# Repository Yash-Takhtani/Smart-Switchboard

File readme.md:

# Smart Switchboard
### Smart switchboard solves a unique problem. Usually smart devices require you to keep the switch on, making the switchboard useless. This smart switchboard solves that problem by making the switches smart directly.

# Features
 - This uses an ESP32 to control relays connected with my lights and a socket. I have a smart fan and the ESP32 will use its API to control the smart fan. 
 - It has 4 push buttons and a rotary encoder switch with RGB LEDs to control the devices.

# Quick Start
To replicate this project, you would want to follow these steps - 
 - Clone the repo and get the production files & firmware files
 - Get the model 3d printed from the .stl files
 - Take a look at the BOM and arrange the parts
 - Refer to the schematic folder and wire up the parts. (You have to have some soldering knowledge) **Be careful when handling wires from mains!**
 - Assemble all the components with non-conductive glue for electronics in the 3D printed model.
 - Enter your wifi credentials in the firmware.
 - Flash the firmware via micropico in the ESP32. 
 - Finally visit your ESP's local IP to access the control panel!

# Schematic
Here is the schematic. 

All the parts should be soldered directly since the microcontroller is to be kept a bit far away from the live AC current wires so that it works the best. Since the circuit is very simple and all the parts are supposed to be spaced out, a PCB is not required and the parts will be soldered directly.

# CAD model
 - This is the model to be 3D printed. It has holes to place the push buttons, LEDs and the rotary encoder switch

 - It also has space to stick a socket in the back. 

 - I measured everything like the screw holes, socket size and the borders with my existing switchboard to ensure everything fits in place

# Firmware
 - The firmware launches a webserver to control all the devices including 3 lights, a socket and a fan. 

 - I have a smart fan with a remote. I also have a IR blaster which I will use to control the fan. The code to control the fan via the IR blaster's API will not be pushed to github for obvious reasons. I dont want people around the world to control my fan. 

 - The firmware is made such that you could seamlessly switch the control between controlling from webserver or with physical buttons. The lights will also update in the switchboard as you change status of any device

# Build
**Check out the [demo video](https://www.youtube.com/shorts/NMJ9t9IXdI0)**

I completed the build and it works! 

I tested it out with a bulb only instead of installing it completely since there's not much I can do (I live in a rented place I am not supposed to mess with their switchboards)

# BOM
 - 1x  3D printed base
 - 1x  ESP32
 - 1x  Rotary Encoder Switch
 - 1x  5V 2A Power Supply
 - 4x  Push buttons
 - 4x  5V 30A Relays
 - 15x WS2812B RGB LEDs
 
For testing out stuff - 
 - 1x  Breadboard
 - 40x jumper wires

# Credits 
## Knob Model - [Jack](https://www.printables.com/model/243409-crown-knob/files)

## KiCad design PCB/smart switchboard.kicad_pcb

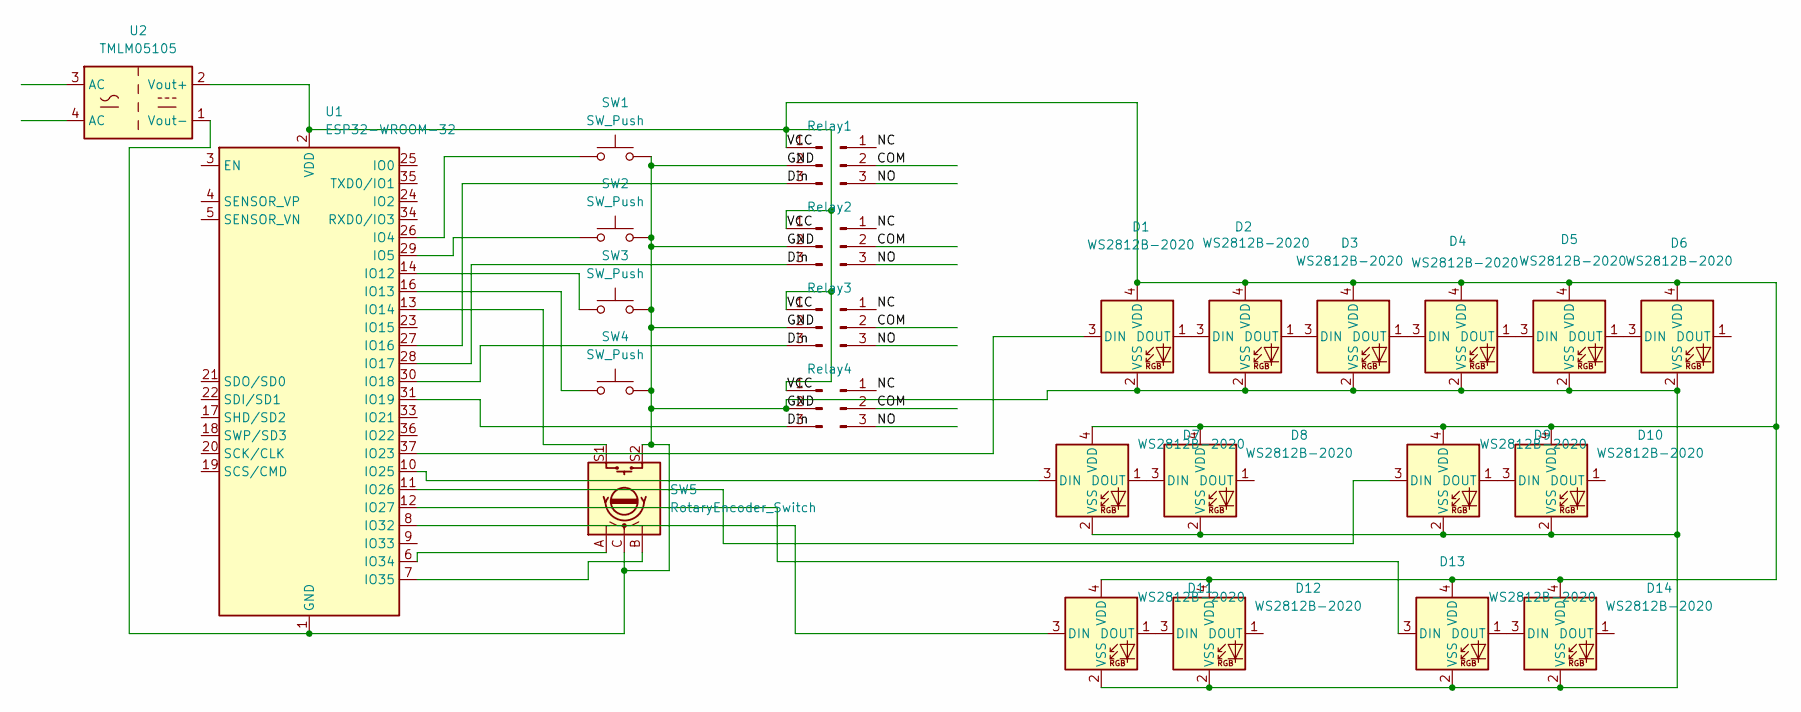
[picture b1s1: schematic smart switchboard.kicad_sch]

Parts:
D1, D2, D3, D4, D5, D6, D7, D8, D9, D10, D11, D12, D13, D14: WS2812B-2020; LED_WS2812B-2020_PLCC4_2.0x2.0mm
J3, J4, J5, J6: Conn_01x03_Pin; PinHeader_1x03_P2.00mm_Vertical
Relay1, Relay2, Relay3, Relay4: Conn_01x03_Pin; PinHeader_1x03_P2.00mm_Vertical
SW1, SW2, SW3, SW4: SW_Push; SW_PUSH_1P1T_6x3.5mm_H4.3_APEM_MJTP1243
SW5: RotaryEncoder_Switch; RotaryEncoder_Alps_EC11E-Switch_Vertical_H20mm
U1: ESP32-WROOM-32
U2: TMLM05105; Converter_ACDC_TRACO_TMLM-05_THT

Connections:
/COM: Relay1.2, Relay2.2, Relay3.2, Relay4.2
/Din: J3.3, J4.3, J5.3, J6.3, U1.27 (IO16), U1.28 (IO17), U1.30 (IO18), U1.31 (IO19)
/GND: D1.2 (VSS), D2.2 (VSS), D3.2 (VSS), D4.2 (VSS), D5.2 (VSS), D6.2 (VSS), D7.2 (VSS), D8.2 (VSS), D9.2 (VSS), D10.2 (VSS), D11.2 (VSS), D12.2 (VSS), D13.2 (VSS), D14.2 (VSS), J3.2, J4.2, J5.2, J6.2, SW1.2, SW2.2, SW3.2, SW4.2, SW5.C, SW5.S2, U1.1 (GND), U1.15 (GND), U1.38 (GND), U1.39 (GND), U2.1 (Vout-)
/NC: Relay1.1, Relay2.1, Relay3.1, Relay4.1
/NO: Relay1.3, Relay2.3, Relay3.3, Relay4.3
/VCC: D1.4 (VDD), D2.4 (VDD), D3.4 (VDD), D4.4 (VDD), D5.4 (VDD), D6.4 (VDD), D7.4 (VDD), D8.4 (VDD), D9.4 (VDD), D10.4 (VDD), D11.4 (VDD), D12.4 (VDD), D13.4 (VDD), D14.4 (VDD), J3.1, J4.1, J5.1, J6.1, U1.2 (VDD), U2.2 (Vout+)
unnamed: D1.3 (DIN), U1.37 (IO23)
unnamed: D1.1 (DOUT), D2.3 (DIN)
unnamed: D2.1 (DOUT), D3.3 (DIN)
unnamed: D3.1 (DOUT), D4.3 (DIN)
unnamed: D4.1 (DOUT), D5.3 (DIN)
unnamed: D5.1 (DOUT), D6.3 (DIN)
unnamed: D7.3 (DIN), U1.10 (IO25)
unnamed: D7.1 (DOUT), D8.3 (DIN)
unnamed: D9.3 (DIN), U1.11 (IO26)
unnamed: D9.1 (DOUT), D10.3 (DIN)
unnamed: D11.3 (DIN), U1.8 (IO32)
unnamed: D11.1 (DOUT), D12.3 (DIN)
unnamed: D13.3 (DIN), U1.12 (IO27)
unnamed: D13.1 (DOUT), D14.3 (DIN)
unnamed: SW1.1, U1.26 (IO4)
unnamed: SW2.1, U1.29 (IO5)
unnamed: SW3.1, U1.14 (IO12)
unnamed: SW4.1, U1.16 (IO13)
unnamed: SW5.S1, U1.13 (IO14)
unnamed: SW5.A, U1.6 (IO34)
unnamed: SW5.B, U1.7 (IO35)

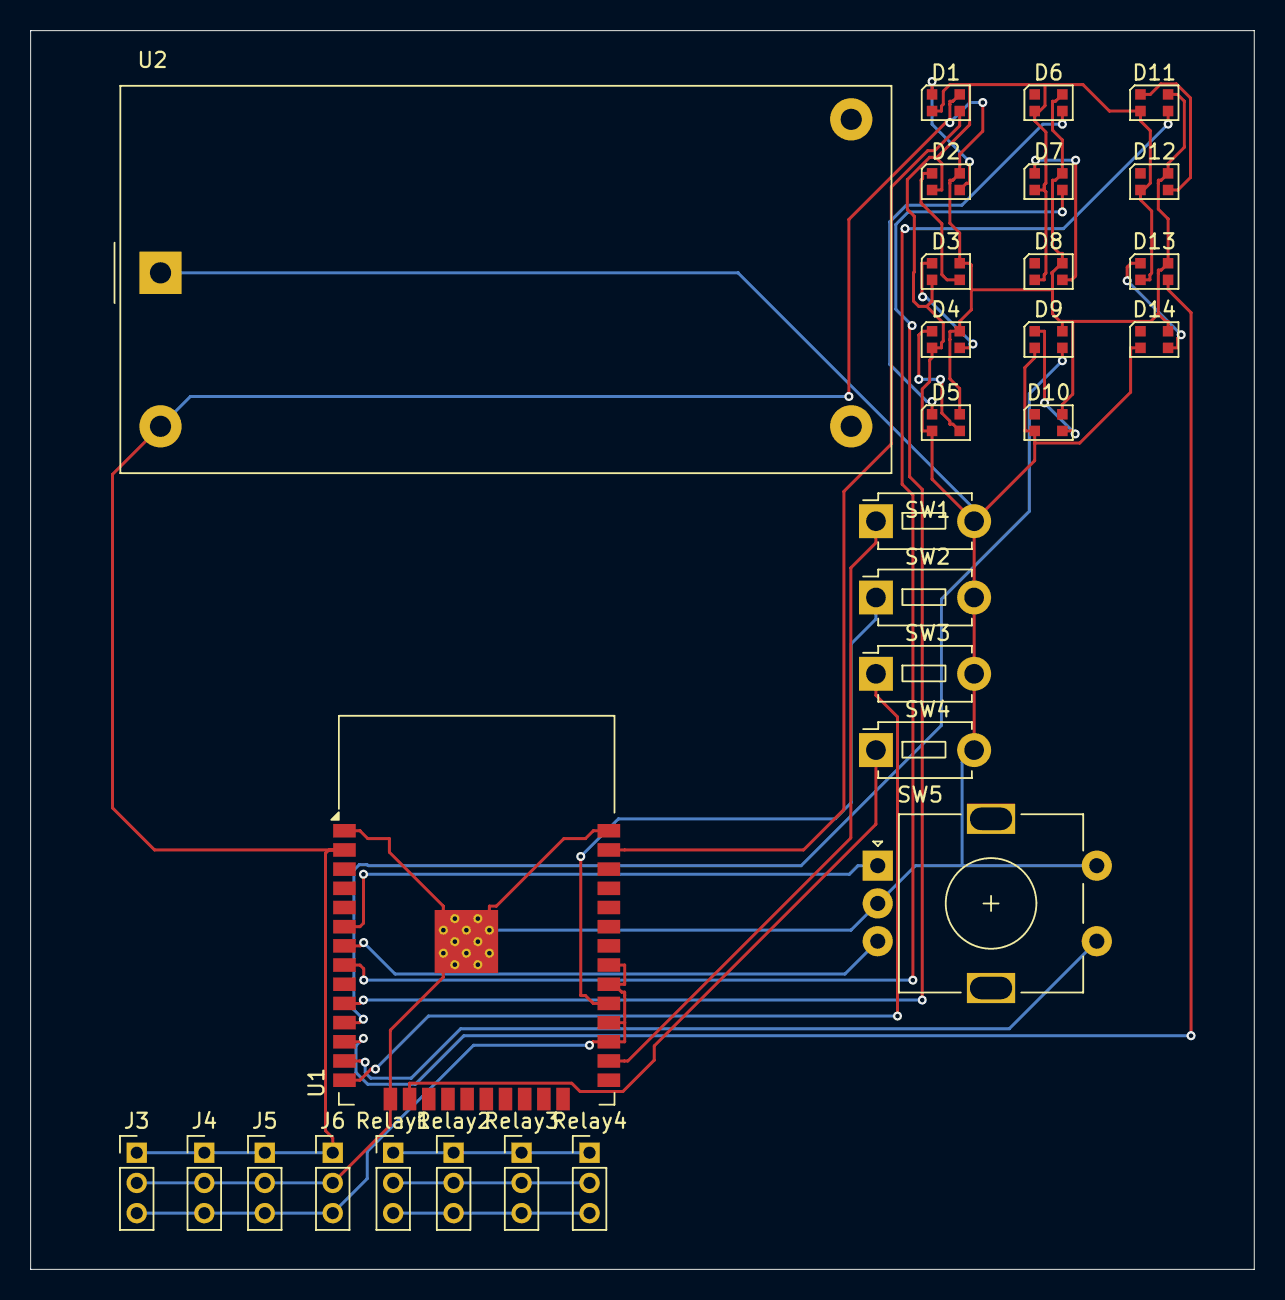
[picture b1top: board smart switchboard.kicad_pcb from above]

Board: 2 copper layers, 81.0 x 82.0 mm, 29 parts (0 on the bottom side), 27 nets.
